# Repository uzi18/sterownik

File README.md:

## repozytorium zawiera: 

* Lucjan (katalog arduino) - sterownik pieca CO na bazie Arduino Mega w tym schematy, wsad i wiele innych
* skrypty w python dla eCoal.pl/bruli.pl dla nie wspierancyh juz sterowników

## Wszelkie błędy, propozycje zmian i dodatkowe funkcje zgłaszamy w [Issues](https://github.com/uzi18/sterownik/issues)
  * [Issues](https://github.com/uzi18/sterownik/issues) zgłaszane przez osoby wspierające Lucjana będą rozpatrywane z pierwszeństwem.  
  * Na [stronie wsparcia](https://www.paypal.me/wsparcieDlaLucjana) w uwagach prosze podawać nr. [issue](https://github.com/uzi18/sterownik/issues), którego sie tyczy.  
  
## Zapraszamy do dyskusji ONLINE - kliknij na link: 

## Podoba Ci się projekt, kliknij i wesprzyj Lucjana:

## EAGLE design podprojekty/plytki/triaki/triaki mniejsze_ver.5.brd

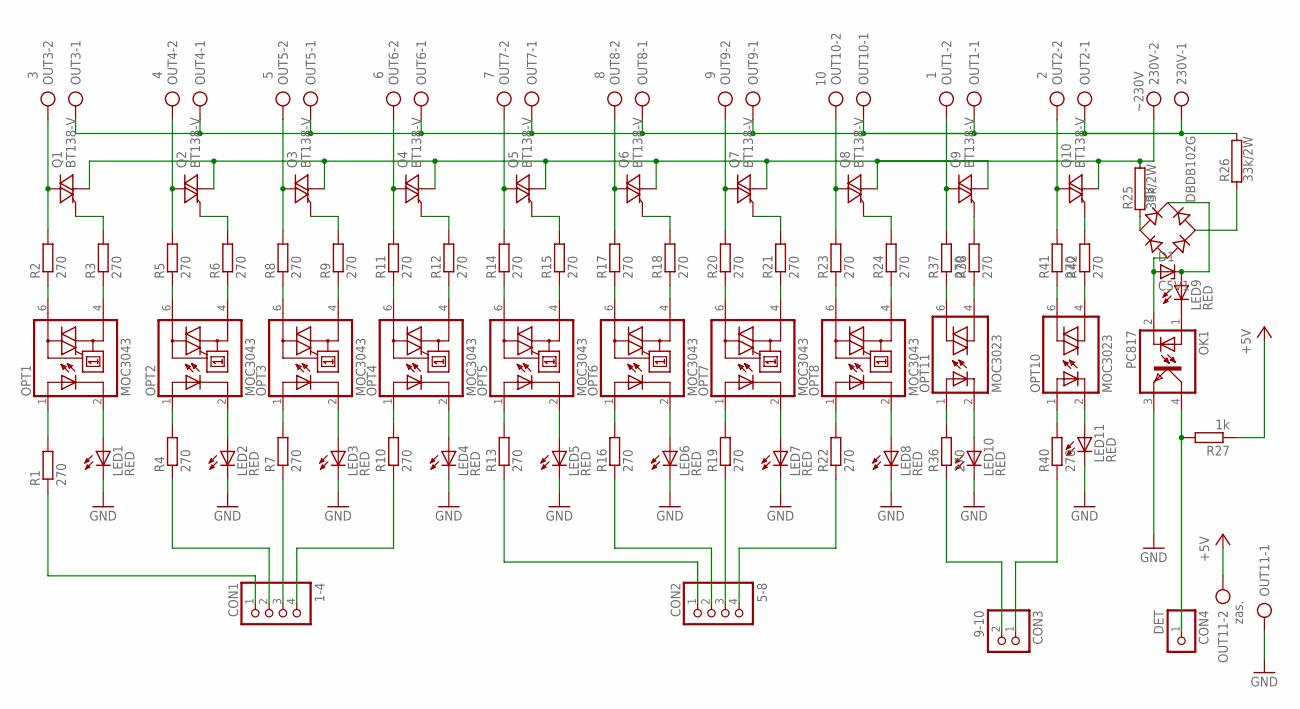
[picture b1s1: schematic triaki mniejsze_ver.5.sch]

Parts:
230V: ~230V; AK500/2
B3: DBDB102G; DB
CON1: 1-4; 1X04
CON2: 5-8; 1X04
CON3: 9-10; 1X02
CON4: DET; 1X01
D1: C5V1; DO35Z10
LED1, LED2, LED3, LED4, LED5, LED6, LED7, LED8, LED9, LED10, LED11: RED; LED3MM
OK1: PC817; DIL04
OPT1, OPT2, OPT3, OPT4, OPT5, OPT6, OPT7, OPT8: MOC3043; DIL06; MPN MOC3041
OPT10, OPT11: MOC3023; DIL06; MPN MOC3021
OUT1: 1; AK500/2
OUT2: 2; AK500/2
OUT3: 3; AK500/2
OUT4: 4; AK500/2
OUT5: 5; AK500/2
OUT6: 6; AK500/2
OUT7: 7; AK500/2
OUT8: 8; AK500/2
OUT9: 9; AK500/2
OUT10: 10; AK500/2
OUT11: zas.; AK500/2
Q1, Q2, Q3, Q4, Q5, Q6, Q7, Q8, Q9, Q10: BT138-V; TO220BV
R1, R2, R3, R4, R5, R6, R7, R8, R9, R10, R11, R12, R13, R14, R15, R16, R17, R18, R19, R20, R21, R22, R23, R24, R36, R37, R38, R40, R41, R42: 270; 0204/7
R25, R26: 33k/2W; AC01
R27: 1k; 0204/7

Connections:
+5V: OUT11.2, R27.1
GND: LED1.K (C), LED2.K (C), LED3.K (C), LED4.K (C), LED5.K (C), LED6.K (C), LED7.K (C), LED8.K (C), LED10.K (C), LED11.K (C), OK1.3 (EMIT), OUT11.1
unnamed: OPT1.4 (A1), R3.1
unnamed: OPT11.1 (A), R36.2
unnamed: LED1.A, OPT1.2 (C)
unnamed: Q1.G, R3.2
unnamed: OUT3.2, Q1.T2 (A2), R2.2
unnamed: OPT10.1 (A), R40.2
unnamed: OPT2.6 (A2), R5.1
unnamed: OPT8.1 (A), R22.2
unnamed: Q2.G, R6.2
unnamed: OPT2.4 (A1), R6.1
unnamed: 230V.1, OUT1.1, OUT2.1, OUT3.1, OUT4.1, OUT5.1, OUT6.1, OUT7.1, OUT8.1, OUT9.1, OUT10.1, R26.2
unnamed: LED2.A, OPT2.2 (C)
unnamed: OPT7.1 (A), R19.2
unnamed: OPT6.1 (A), R16.2
unnamed: OPT3.6 (A2), R8.1
unnamed: OUT5.2, Q3.T2 (A2), R8.2
unnamed: Q3.G, R9.2
unnamed: OPT3.4 (A1), R9.1
unnamed: LED9.K (C), OK1.1 (A)
unnamed: OPT5.1 (A), R13.2
unnamed: LED3.A, OPT3.2 (C)
unnamed: OPT4.1 (A), R10.2
unnamed: OPT3.1 (A), R7.2
unnamed: OPT4.6 (A2), R11.1
unnamed: OUT6.2, Q4.T2 (A2), R11.2
unnamed: Q4.G, R12.2
unnamed: OPT4.4 (A1), R12.1
unnamed: OPT2.1 (A), R4.2
unnamed: CON1.3, R7.1
unnamed: LED4.A, OPT4.2 (C)
unnamed: CON1.4, R10.1
unnamed: CON1.2, R4.1
unnamed: OPT5.6 (A2), R14.1
unnamed: OUT7.2, Q5.T2 (A2), R14.2
unnamed: Q5.G, R15.2
unnamed: OPT5.4 (A1), R15.1
unnamed: CON1.1, R1.1
unnamed: CON2.3, R19.1
unnamed: LED5.A, OPT5.2 (C)
unnamed: B3.+, D1.C, LED9.A
unnamed: OPT6.6 (A2), R17.1
unnamed: OUT8.2, Q6.T2 (A2), R17.2
unnamed: Q6.G, R18.2
unnamed: OPT6.4 (A1), R18.1
unnamed: B3.AC1, R25.1
unnamed: B3.AC2, R26.1
unnamed: LED6.A, OPT6.2 (C)
unnamed: CON2.4, R22.1
unnamed: CON2.2, R16.1
unnamed: OPT7.6 (A2), R20.1
unnamed: OUT9.2, Q7.T2 (A2), R20.2
unnamed: Q7.G, R21.2
unnamed: OPT7.4 (A1), R21.1
unnamed: Q9.G, R38.2
unnamed: B3.-, D1.A, OK1.2 (C)
unnamed: LED7.A, OPT7.2 (C)
unnamed: CON2.1, R13.1
unnamed: CON3.1, R40.1
unnamed: OPT8.6 (A2), R23.1
unnamed: OUT10.2, Q8.T2 (A2), R23.2
unnamed: Q8.G, R24.2
unnamed: OPT8.4 (A1), R24.1
unnamed: CON3.2, R36.1
unnamed: OPT11.4 (A1), R38.1
unnamed: LED8.A, OPT8.2 (C)
unnamed: OPT10.4 (A1), R42.1
unnamed: Q10.G, R42.2
unnamed: LED10.A, OPT11.2 (C)
unnamed: OPT11.6 (A2), R37.1
unnamed: OUT1.2, Q9.T2 (A2), R37.2
unnamed: 230V.2, Q1.T1 (A1), Q2.T1 (A1), Q3.T1 (A1), Q4.T1 (A1), Q5.T1 (A1), Q6.T1 (A1), Q7.T1 (A1), Q8.T1 (A1), Q10.T1 (A1), R25.2
unnamed: OPT10.6 (A2), R41.1
unnamed: LED11.A, OPT10.2 (C)
unnamed: OUT2.2, Q10.T2 (A2), R41.2
unnamed: CON4.1, OK1.4 (COL), R27.2
unnamed: OUT4.2, Q2.T2 (A2), R5.2

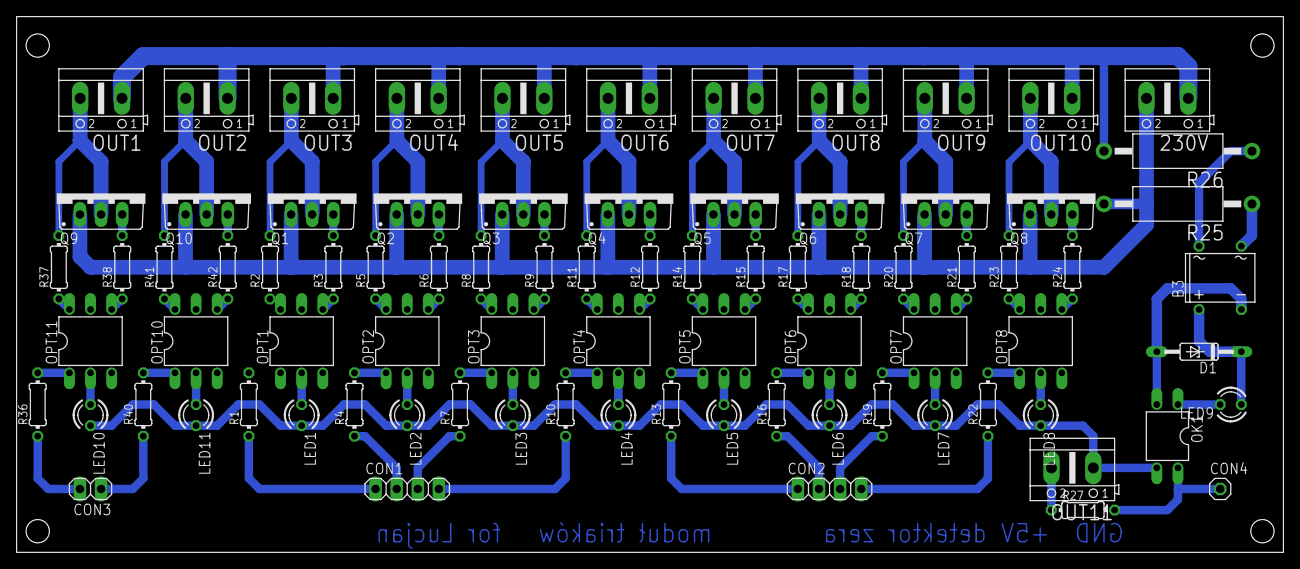
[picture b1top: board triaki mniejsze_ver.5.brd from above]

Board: 2 copper layers, 152.4 x 64.4 mm, 83 parts (0 on the bottom side), 78 nets.

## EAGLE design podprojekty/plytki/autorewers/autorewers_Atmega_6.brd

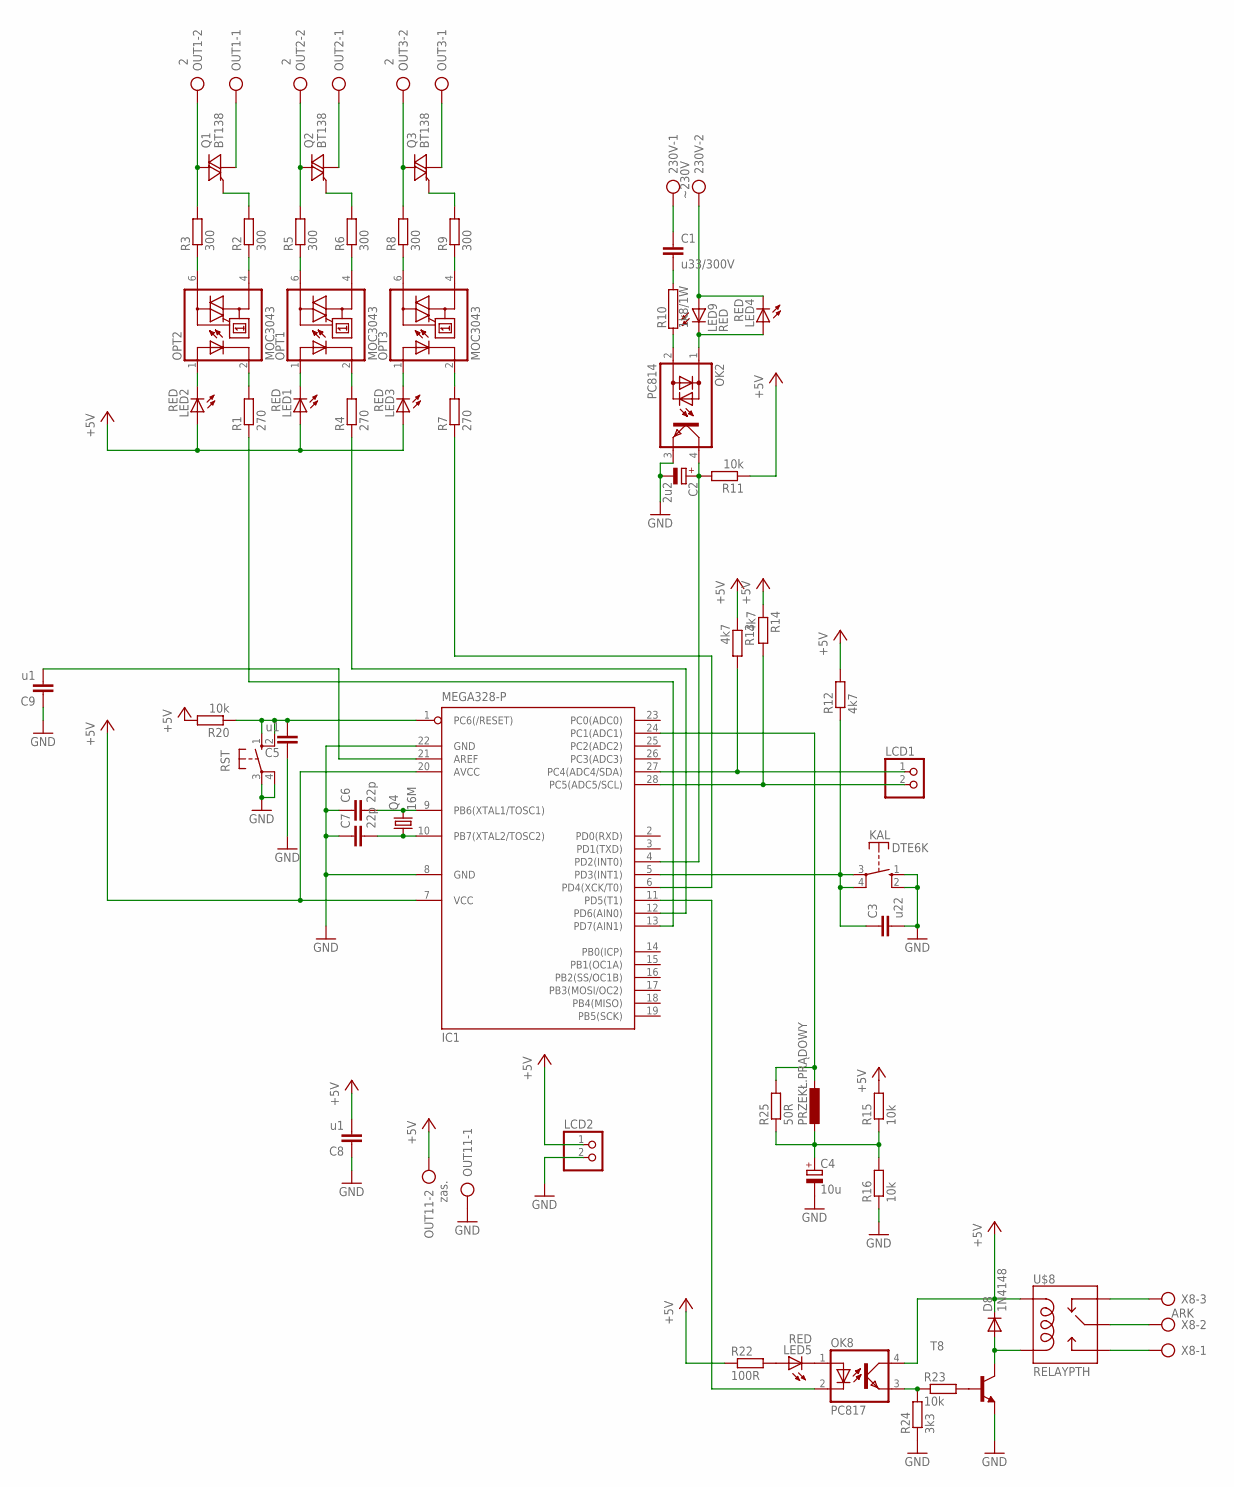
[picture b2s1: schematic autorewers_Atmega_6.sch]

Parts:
230V: ~230V; AK500/2
C1: u33/300V; C225-087X268
C2: 2u2; B45181A
C3: u22; C050-025X075
C4: 10u; B45181A
C5, C8, C9: u1; C050-025X075
C6, C7: 22p; C050-025X075
D8: 1N4148; DO35-10
IC1: MEGA328-P; DIL28-3
KAL: DTE6K
LCD1, LCD2: PINHD-1X2; 1X02
LED1, LED2, LED3, LED4, LED5, LED9: RED; LED3MM
OK2: PC814; DIL04
OK8: PC817; DIL04
OPT1, OPT2, OPT3: MOC3043; DIL06; MPN MOC3041
OUT1, OUT2, OUT3: 2; AK500/2
OUT11: zas.; AK500/2
PRZEKŁ.PRĄDOWY: L-EU2200-12.7; 2200-12.7
Q1, Q2, Q3: BT138; TO220BV
Q4: 16M; HC49/S
R1: 270; 0204/7
R2, R3, R5, R6, R8, R9: 300; 0204/7
R4: 270; 0204/5
R7: 270; 0617/22
R10: 1k8/1W; AC01
R11: 10k; 0207/10
R12, R13, R14: 4k7; 0204/7
R15, R16: 10k; 0204/7
R20: 10k; 0207/15
R22: 100R; 0207/10
R23: 10k; 0204/5
R24: 3k3; 0204/7
R25: 50R; 0204/7
RST: 10-XX; B3F-10XX
T8: BC237-NPN-TO92-CBE; TO92-CBE
U$8: RELAYPTH; SRD-05VDC-SL-C
X8: ARK; AK300/3

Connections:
+5V: C8.2, D8.C, IC1.7 (VCC), IC1.20 (AVCC), LCD2.1, LED1.A, LED2.A, LED3.A, OK8.4 (COL), OUT11.2, R11.1, R12.2, R13.1, R14.1, R15.2, R20.2, R22.1, U$8.COIL1
GND: C2.-, C3.2, C4.-, C5.1, C6.1, C7.1, C8.1, C9.1, IC1.8 (GND), IC1.22 (GND), KAL.1 (S), KAL.2 (S), LCD2.2, OK2.3 (E), OUT11.1, R16.1, R24.1, RST.3, RST.4 (P1), T8.E
unnamed: OUT1.1, Q1.T1 (A1)
unnamed: C2.+, IC1.4 (PD2(INT0)), OK2.4 (C), R11.2
unnamed: LED2.K (C), OPT2.1 (A)
unnamed: OPT2.2 (C), R1.2
unnamed: OPT1.6 (A2), R5.1
unnamed: Q2.G, R6.2
unnamed: OPT1.4 (A1), R6.1
unnamed: OPT2.6 (A2), R3.1
unnamed: OUT2.2, Q2.T2 (A2), R5.2
unnamed: Q1.G, R2.2
unnamed: OPT2.4 (A1), R2.1
unnamed: LED1.K (C), OPT1.1 (A)
unnamed: OPT1.2 (C), R4.2
unnamed: OPT3.6 (A2), R8.1
unnamed: Q3.G, R9.2
unnamed: OPT3.4 (A1), R9.1
unnamed: OUT3.2, Q3.T2 (A2), R8.2
unnamed: LED3.K (C), OPT3.1 (A)
unnamed: OPT3.2 (C), R7.2
unnamed: 230V.2, LED4.K (C), LED9.A
unnamed: OUT3.1, Q3.T1 (A1)
unnamed: C1.2, R10.2
unnamed: OK2.2 (AC2), R10.1
unnamed: LED4.A, LED9.K (C), OK2.1 (AC1)
unnamed: C3.1, IC1.5 (PD3(INT1)), KAL.3, KAL.4, R12.1
unnamed: 230V.1, C1.1
unnamed: IC1.12 (PD6(AIN0)), R4.1
unnamed: IC1.6 (PD4(XCK/T0)), R7.1
unnamed: IC1.24 (PC1(ADC1)), PRZEKŁ.PRĄDOWY.1, R25.2
unnamed: IC1.13 (PD7(AIN1)), R1.1
unnamed: C6.2, IC1.9 (PB6(XTAL1/TOSC1)), Q4.2
unnamed: C4.+, PRZEKŁ.PRĄDOWY.2, R15.1, R16.2, R25.1
unnamed: U$8.SWOPEN, X8.1
unnamed: U$8.SWCLOSED (SWCLOSE), X8.3
unnamed: LED5.K (C), OK8.1 (A)
unnamed: C5.2, IC1.1 (PC6(/RESET)), R20.1, RST.1 (S), RST.2 (S1)
unnamed: IC1.11 (PD5(T1)), OK8.2 (C)
unnamed: LED5.A, R22.2
unnamed: IC1.27 (PC4(ADC4/SDA)), LCD1.1, R13.2
unnamed: C7.2, IC1.10 (PB7(XTAL2/TOSC2)), Q4.1
unnamed: IC1.28 (PC5(ADC5/SCL)), LCD1.2, R14.2
unnamed: OUT2.1, Q2.T1 (A1)
unnamed: OK8.3 (EMIT), R23.1, R24.2
unnamed: R23.2, T8.B
unnamed: D8.A, T8.C, U$8.COIL0
unnamed: U$8.SWCOMMON, X8.2
unnamed: OUT1.2, Q1.T2 (A2), R3.2
S$1: C9.2, IC1.21 (AREF)

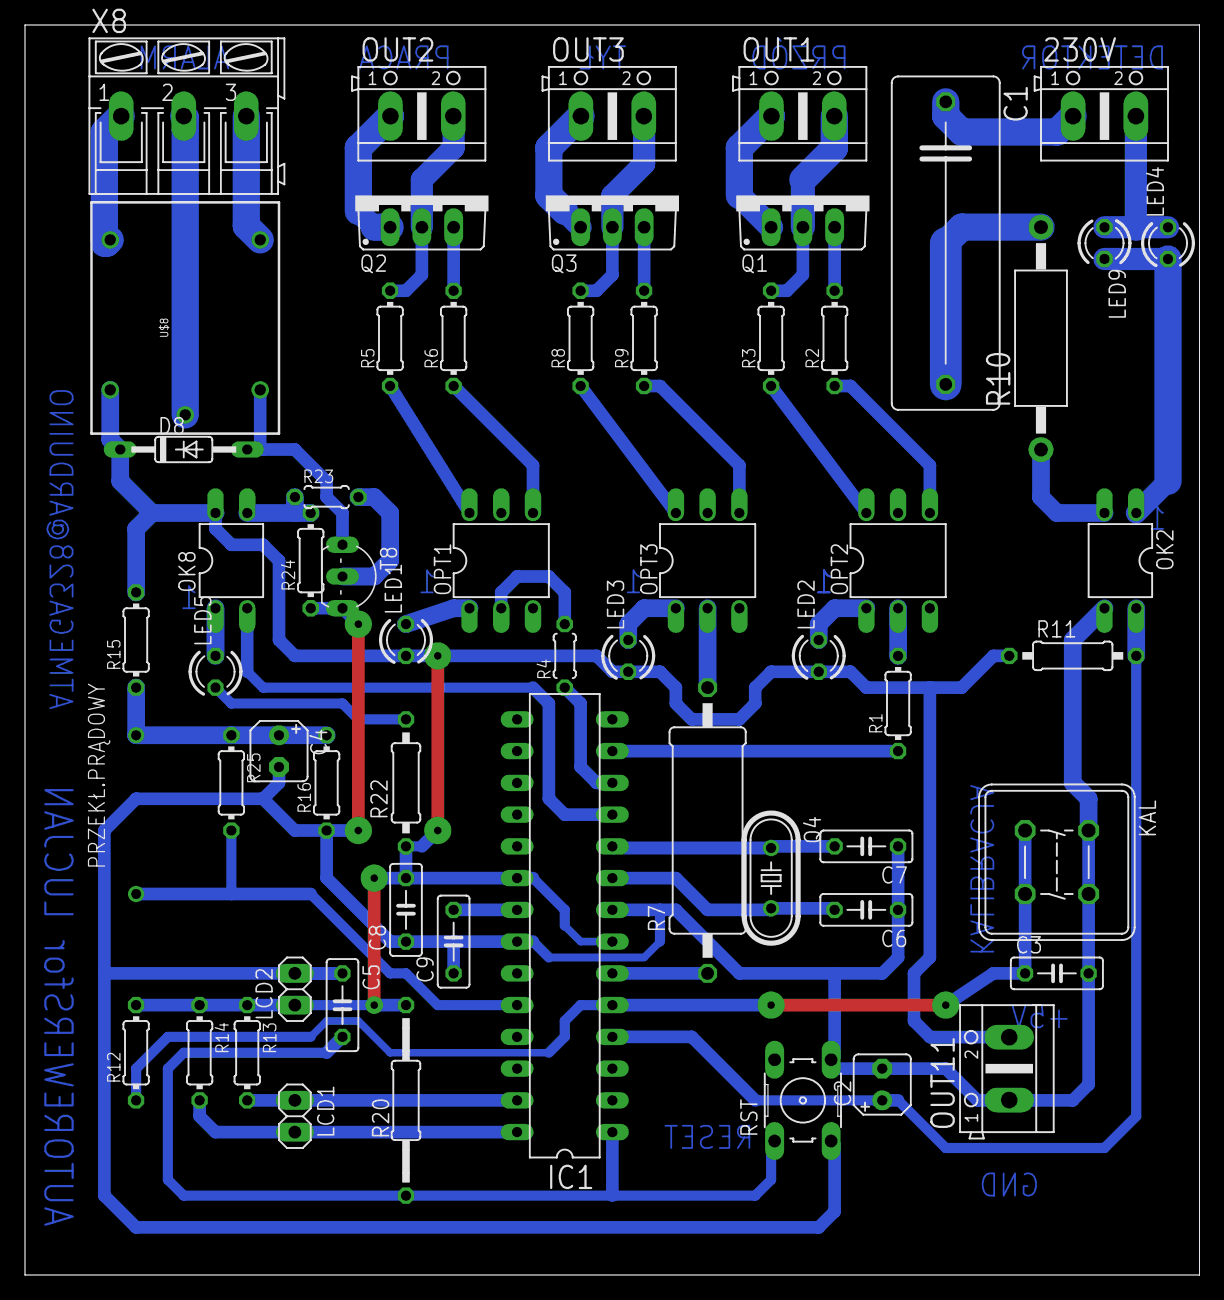
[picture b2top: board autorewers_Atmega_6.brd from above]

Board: 2 copper layers, 94.0 x 100.0 mm, 60 parts (0 on the bottom side), 50 nets.

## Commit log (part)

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2015-10-25 - blokada rozpedu
2015-10-25 - wywalenie rozpedu - nie dziala
2015-10-27 - widelki uzytkownika dla podawania,postoju i dmuchania
2015-10-27 - poprawne wyliczanie mocy - zgodnie z moc_100
2015-10-27 - wiecej info ...
2015-10-27 - opoznienie
2015-10-28 - dodanie informacji o zuzyciu wegla ...
2015-10-29 - ustawiamy zadana gdy delta < 0
2015-11-14 - poprawienie bledu gdy nowe_podawanie jest ponizej 1
2015-11-16 - dodanie importowania konfiguracji z pliku zewnetrznego skopiowanie parametrow do plikow zewnetrznych
2015-11-16 - 4 plus uzywa teraz konfiguracji zewnetrznej
2015-11-17 - 10plush: dodanie sprawdzanie konfiguracji co 10s. i jej aktualizacje. dodane ubijanie watkow i wylaczenie sprzetu przy zamykaniu
2015-11-18 - 10plush: konfiguracja z magic byte, moga byc teraz polski znaki w pliku
2015-11-18 - TRK: update wersji
2015-11-18 - brakujace importy
2015-11-19 - poprawki
2015-11-21 - na potrzeby testow
2015-11-22 - aktualizacja konfiguracji poprzez google docs chwilowo bez aktualizacja pliku ...
2015-11-25 - przeniesienie wentylatora DC na pin 12 - pin 13 - heartbeat
2015-11-25 - aktualizacja informacji o podciagnieciu pinu 12 do +5V
2015-11-27 - nazwa modulu do polaczenia rs232
2015-11-28 - dodano nowa opcje w konfiguracji - zezwalajaca na modyfikacje plikow dodano modyfikacje pliku konfiguracji poprawiono błąd sprawdzania tylko 1 arkusza dodano zabezpieczenia przed wysypaniem sie skr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
2015-11-29 - dodatkowy test czy dostepna jest lista elementow
2015-11-29 - sprawdzamy element tablicy
2015-12-01 - sprawdzamy moc_100 - blad /0
2015-12-08 - dodanie rozpedu,dopalania i tla - dzialaja tylko w trybie automat - dodanie odczytu pliku konfiguracyjnego config.txt na karcie SD jego zawartosc:
    IP1 = 192
    IP2 = 168
    IP3 = 1
    IP4 = 3
    ustawi IP na 192.168.1.3
2015-12-09 - aktualizacja strony www, dla najnowszego pliku hex
2015-12-10 - www: angular aktualizacja do 1.1.5
2015-12-10 - www: zmiana ilosci aktualizacji danych
2015-12-13 - www: tekst jako utf8
2015-12-13 - www: dodanie przycisku zapisz w konfiguracji polaczenia
2016-02-04 - zmieniona predkosc terminala (115200,8N1) - dodane przeszukiwanie magistrali na DS18xx - dodane wywolanie ze strony "/reset" restart arduino przydatne po aktualizacji pliku config.txt
2016-02-06 v.0.1.0.5 - www: dodanie miejsca na wersje sterownika
2016-02-06 v 0.1.0.8 - dodanie wywolania do zmiany modulacji w trakcie pracy sterownika /modulacja0 - brak modulacji dmuchawy /modulacja1 - modulacja dmuchawy w trybie auto /modulacja2 - modulacja dmuchawy w tr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
2016-02-08 Create schemat polaczen sterownika
2016-02-08 v 0.1.0.13 - porzadki w kodzie dmuchawy
2016-02-08 v 0.1.0.15 - dodanie maszyny stanow dla czujnikow dallas
2016-02-11 v 0.1.0.17 www: dodanie zapisu konfiguracji ze strony
2016-02-29 Create dokumenty
2016-03-06 - www: aktualizacja sekcji z temperaturami
2016-03-06 v0.1.0.20 po wstepnych testach dziala ok - usunieci pliku test - www: drobna zmiana koloru
2016-03-07 Added files via upload
    Schemat połączeń sterownika
2016-03-08 v0.1.0.23 reset magistrali 1wire przed skanowaniem - aktywacja watchdoga 8s. - zwis spowoduje reset
2016-03-09 v0.1.0.24 alarm podajnika wylacza dmuchawe - przekaznik wylaczony i moc ustawiona na 0% alarm na ten czas mozna zresetowac tylko przez reset sterownika (np. przez strone www)
2016-03-13 v0.1.0.27 uzupelnienie pakietu dla strony www o dodatkowe dane
2016-03-16 v0.1.0.30 dodanie algorytmu RR plus wiecej info nizej ... nie forsujemy podajnika i wentylatora jesli nie jest to algorytm ECOAL dodanie algorytmu RR parametry dla RR (opis w pliku tekstowym) funkcja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
2016-03-18 v0.1.0.33 - dodanie pracy w szerszej histerezie dla RR/RRM - histereza w 0.1deg
2016-03-21 v0.1.0.36 ograniczenie danych na terminalu do minimum, wyslanie znaku V na terminal lub opcja V=1 w pliku konfiguracyjnym zal/wylacza te informacje (m.in. statystyki)
2016-03-24 www: dodanie parametru predkosci podawania podajnika
2016-03-27 v0.1.0.39 - dodanie wsparcia dla wyjsc z aktywnym stanem niskim (moduly przekaznikow) 24 - podajnik [sygnał odwrócony - stan aktywny niski (0VDC)] 25 - pompa CO [sygnał odwrócony] 26 - pompa CWU1 [sy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
    UWAGA! Z czasem zostanie to ujednolicone w formie konfiguracji
2016-03-28 www: bazujemy na sofcie 0.1.0.41, optymalizacja strony i usuniecie zbednych rzeczy
2016-04-01 Added files via upload
    Schemat połaczeń sterownika
2016-04-06 - www: aktualizacja danych na stronie, dodanie przewidywanego zasypu - www: drobna kosmetyka
2016-04-09 - www: dodanie ograniczenia dla minimum w polach
2016-09-14 - Tester PWM v.2.1 - drobne poprawki
2016-09-25 v0.1.0.48: dodanie obslugi pompki cyrkulacyjnej, w tym opcji w konfiguracji
2016-09-25 v.0.1.0.50 - poprawienie timera od pompy cyrkulacji
2016-09-28 v0.1.0.53 - zawor4D: poprawka na mikrokroki przy otwieraniu - uciszenie statusu pompy cyrkulacyjnej
2016-10-08 v0.1.0.56 - dodanie alarmu - PRZEPALONY BEZPIECZNIK - dodanie monitorowania detektor 0 sieci i triaka - nie pobieramy czasu z NTP jesli nie ma sieciowki - histereza CWU od 0-10deg (parametr 0-100)
2016-10-10 - schemat przeniesiony do katalogu schematy
2016-10-17 v0.1.0.58 - dodanie diagnostyki modulacji dmuchawy - dodanie diagnostyki dmuchawy - optymalizacja sterowania pompami - optymalizacja sterowania kontroli RTC - optymalizacja sterowania zaworem 4D - po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
2016-10-18 v0.1.0.60 - zawor 4D otwieramy poprawnie po osiagnieciu t_max pieca - termostat pokojowy w pelnych stopniach (ZAWOR4D-OBNIZONA=3 - 3 deg.) - termostat pokojowy - odwrocenie dzialania styku zwarty A6 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
2016-10-28 v0.1.0.62 - 4D: po uzyskaniu t.zadanej czekamy na pomiar ustalony czas - ECOAL: info o bledach polaczenia - TRIAC: dodanie informacji o zakluceniach - MAX31855K dodanie filtrowania
2016-11-01 dodanie linku ze wsparciem
2016-11-03 v0.1.0.65 - RTC: czas zimowy - buzzer na pinie 31, sygnalizuje alarm - www: mozliwosc skasowania bledu ze strony
2016-11-05 v0.1.0.66 - sterowanie triakiem dmuchawy (A13) zdublowane na pin 32
2016-11-12 v0.1.0.69 - fix warningu kompilatora - LCD: dodanie informacji o temperaturach CO/CWU podczas pracy - LCD: dodanie obslugi LCD - LCD: dodanie monitu o wersji Lucjana podczas uruchamiania - dodanie wy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
2016-11-17 v0.1.0.72 -Z4D: poprawienie wczytywania trybu pracy
2016-11-17 - aktualizacja opisu polaczen dla MAX31855K
2016-11-22 v0.1.0.75 - dodanie zegarka na LCD
2016-11-23 v0.1.0.78 - LCD: dodanie strony z alarmami
2016-11-29 v0.1.0.81 - LCD: menu alarmow - klikniecie kasuje alarm - dodanie do zapytania /dallas informacji czy zmapowany (m:1 - TAK) - zmiana sposobu obslugi alarmow
2016-11-30 v0.1.0.84 - dodanie trybu recznego - LCD: dodanie obslugi trybu recznego - podajnik przeniesienie sterowania w jedno miejsce
2016-12-01 v0.1.0.87 - dodanie mozliwosci symulacji czujnikow zmapowanych jako SOFT[] - poprawienie informacji o statusie sterowania triakiem - dodanie informacji o braku alarmu dla komendy a
2016-12-13 v0.1.0.88 - DALLAS: dodanie informacji o ilosci bledow komunikacji - dodanie typu czujnika BRAK[] - poprawki przy monitorowaniu detektora - 4 w konsoli - dodanie zapytania t.json - Z4D: poprawka prac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
2017-01-16 v0.1.0.89 - RS232: wysylamy komunikat START po przygotowaniu systemu do pracy - RTC: zmiana sposobu wydruku informacji o czasie - TRIAK: zmiana sposobu pomiaru ilosci polokresow - dodanie wstepnej an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
2017-01-20 v0.1.0.91: - dodanie mozliwosci mapowania MAX6675K przyklad: TSPALIN = MAX6675[0] - dodanie obslugi MAX6675K pin CS - 49 - zmiana podlaczenia pin CS z MAX31855 A7->48 - uzywamy wlasnej biblioteki do 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
2017-01-22 v0.1.0.94 - LCD: poprawka dla strony z TZEW - nie wyczyszczony znak - dodanie filtrowania pomiaru dla MAX6675 - mapowac z opcja [1] tj. TSPALIN=MAX6675[1]
2017-01-24 Update README.md
    update
2017-01-29 v0.1.0.97 - pompa CO - dodanie trybu cyklicznego - NTP odpytujemy co 24h - wstepna wersja testowa pracy RRM z tlem - domyslnie wylaczona
2017-01-31 v0.1.0.100 - mapowanie: poprawienie wstępnego odczytu
2017-01-31 v0.1.0.103 - dallas: tablice drukujemy przy uruchomieniu tylko jesli znaleziono czujniki - dallas: nie drukujemy czasu pobierania danych z czujnikow - NTP: komenda N w terminalu pobiera czas z NTP
2017-02-06 v0.1.0.106 - przechodzimy z tła w podtrzymanie po przebiciu ponad zadana+przebicie
2017-02-06 v0.1.0.109 - dodanie statystyk do algorytmu wielu mocy
2017-02-08 - dodanie katalogu na plugin Domoticz
2017-02-12 - zwijamy wszystko w petle
2017-02-12 Domoticz - poprawki zgodnosci python3 i python2
2017-02-14 - Domoticz - dodanie testu parametrow konfiguracji
2017-02-19 - esp-link firmware
2017-02-19 - Domoticz: dodanie polaczenia poprzez esp-link
2017-02-25 - Nettemp,Domoticz: prosty test poprawnosci danych przed wyslaniem
2017-03-05 - schemat detektora 0 by Marek Gajos
2017-03-11 v0.1.0.117 - uaktywnienie mozliwosci sterowania zaworem 4D z panela LCD
2017-04-02 v0.1.0.119 - dodanie algorytmu zasypowego: ZASYP_MOC=30 ustawia moc nadmuchu dla trybu zasypowego
2017-04-07 v0.1.0.121 - RTC_ZIMA=1 wymusza czas zimowy dla NTP
2017-05-21 - poprawka do skryptu 10plush.py Marka, w trybie autolato jesli t.wew osiagnie zadana wylaczamy pompe CO
2017-06-27 v0.1.0.123 - w trybie lato dodanie mozliwosci ustawienia odrebnego czasu miedzy podtrzymaniami: RR_PODTRZYMANIE_CZAS_LATO - dodanie ograniczenia krotnosci podnoszenia zaru domyslnie wylaczone - PODAJ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
2017-07-30 v0.1.0.125 - dmuchawa: dodanie alternatywnego algorytmu regulacji mocy nadmuchu DM_TYP=1 nowy DM_TYP=0 stary - dodanie nowego portu szeregowego TXD1/RXD1 do komunikacji ze sterownikiem na razie bez w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
2017-08-14 v0.1.0.128 - dodanie sygnalu odwroconego dla dmuchawy AC na pin 33
2017-08-19 0.1.0.129.1 - LCD: dodanie ustawien dla algorytmu zasypowego - LCD: drobne poprawki znakow - poprawienie oznaczen wyjsc cyfrowych
2017-09-09 v0.1.0.129.4 - WWW: dodanie obslugi autoryzacji w trybie Basic login admin haslo lucjan - RTC: wstepne poprawki zwiazane z DST - WWW: optymalizacje - WWW: dodanie mozliwosci ustawienia wlasnego hasla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
2017-09-27 0.1.0.129.7 - poprawki dla dopalania w algorytmie RRM2 - czas podtrzymania = 0 wylacza funkcje podtrzymania
2017-10-17 0.1.0.130.1 - ograniczenie zakresu dla cyklicznej pracy pompy CO do 240s/240s
2017-10-31 v0.1.0.130.3 - wstepne wsparcie dla podajnika tlokowego - dodanie parametrow dla podajnika tlokowego - poprawka zakresu czasu dla naweglania
2017-11-05 - usprawnienia w skryptcie Domoticz/Nettemp
2017-11-12 - dodanie pomiarow sprawnego detektora
2017-11-19 Update README.md
    dodanie linku do Chat-a
2017-12-31 v0.1.0.130.7 - poprawki dla statystyk - poprawki dla alarmu tmin - teraz podajemy temperature dla alarmu
2018-01-03 v0.1.0.130.9 - dodanie statystyki bledow polaczenia
2018-01-09 v0.1.0.130.12 - przepisanie komunikacji z serwerem na maszyne stanow, mniej obciaza
2018-01-10 - domoticz pokazujemy odliczanie w konsoli
2018-01-15 - www: dodanie przycisku do przeladowania konfiguracji
2018-01-19 v0.1.0.130.16 - DALLAS: mozna zmniejszyc ilosc informacji w terminalu - tlok: poprawka dzialania na koncu cyklu i wydluzenie czasu dla czujnika - tlok: drobne poprawki
2018-01-20 - Domoticz: zwiekszenie timeout dla serial/esp-link
2018-01-29 Opis parametrów na Wiki
2018-01-31 v0.1.0.130.20 - przy alarmie niskiej temperatury pieca po spadku temperatury ponizej minimalnej przechodzimy w tryb reczny - poprawki dla KTY81 - poprawki odczytu wejsc analogowych
2018-02-04 - www: domyslnie wczytujemy poprawna strone
2018-02-04 v0.1.0.130.23 - poprawka alarmu stanu minimalnego w zasobniku - poprawka dla alarmu temperatury minimalnej
2018-02-08 v0.1.0.130.26 - www: dodanie informacji procentowej z czujnika poziomu - CWU: poprawienie pracy priorytetu uruchamiamy tylko gdy trzeba dogrzac - dallas i ecoal/bruli: przygotowanie danych poczatkowy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
2018-02-28 - Domoticz: dodanie mozliwosci wysylania poziomu podajnika
2018-06-08 v0.1.0.130.29 - poprawka dla cwu2 w trybie roznicowym
2018-06-25 - porzadki
2019-02-24 domoticz - ograniczenie wielosci plikow logow
